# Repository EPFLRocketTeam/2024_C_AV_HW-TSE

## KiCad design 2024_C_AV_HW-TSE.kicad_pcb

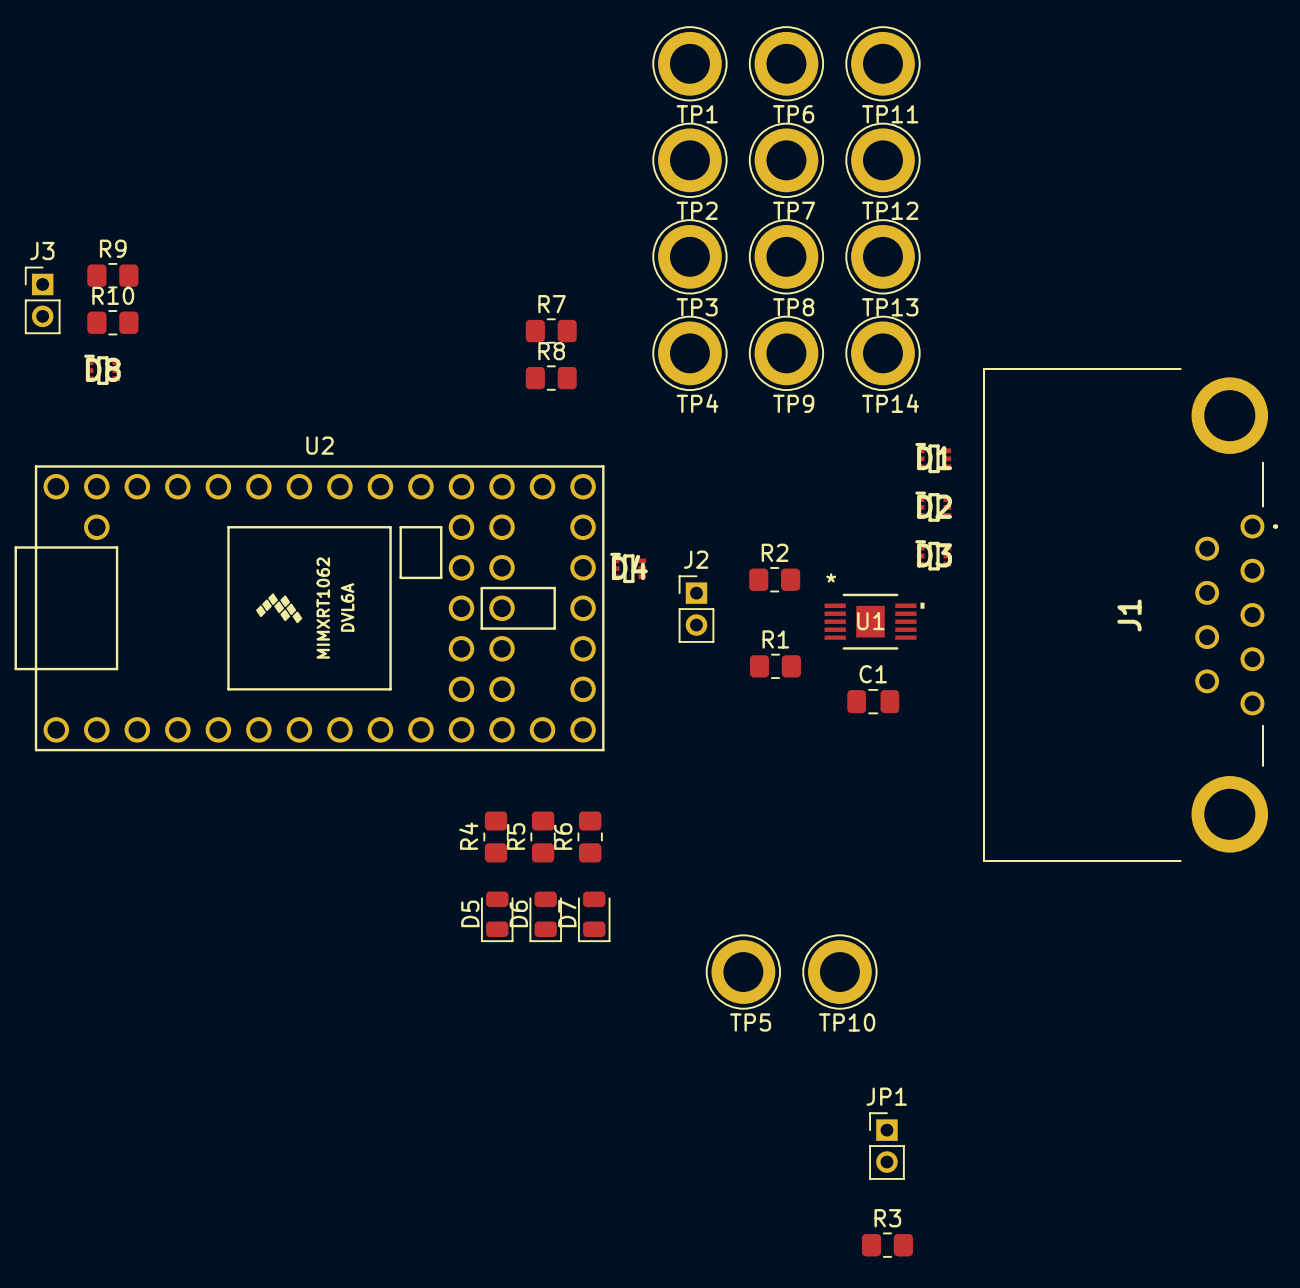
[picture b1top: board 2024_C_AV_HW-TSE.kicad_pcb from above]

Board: 2 copper layers, 39 parts (0 on the bottom side), 23 nets, no tracks yet.

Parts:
C1: 2.2u; C_0805_2012Metric_Pad1.18x1.45mm_HandSolder
D1, D2, D3, D4, D8: TPD2E1B06DRLR; SOTFL50P160X60-6N
D5, D6, D7: LED; LED_0805_2012Metric
J1: Spine Connector; G17C0910132EU
J2: I2C Bypass; PinHeader_1x02_P2.00mm_Vertical
J3: USART Bypass; PinHeader_1x02_P2.00mm_Vertical
JP1: Master/Slave Select; PinHeader_1x02_P2.00mm_Vertical
R1, R2: 4.7k; R_0805_2012Metric_Pad1.20x1.40mm_HandSolder
R3: 30k; R_0805_2012Metric_Pad1.20x1.40mm_HandSolder
R4, R5, R6: 220R; R_0805_2012Metric_Pad1.20x1.40mm_HandSolder
R7: 51k; R_0805_2012Metric_Pad1.20x1.40mm_HandSolder
R8: 47k; R_0805_2012Metric_Pad1.20x1.40mm_HandSolder
R9, R10: 0R; R_0805_2012Metric_Pad1.20x1.40mm_HandSolder
TP1: 5V Spine; TestPoint_Loop_D3.80mm_Drill2.5mm
TP2: 3V3 Spine; TestPoint_Loop_D3.80mm_Drill2.5mm
TP3: 5V Meas.; TestPoint_Loop_D3.80mm_Drill2.5mm
TP4: 3V3 Teensy; TestPoint_Loop_D3.80mm_Drill2.5mm
TP5: GND Ref; TestPoint_Loop_D3.80mm_Drill2.5mm
TP6: LED 1; TestPoint_Loop_D3.80mm_Drill2.5mm
TP7: LED 2; TestPoint_Loop_D3.80mm_Drill2.5mm
TP8: LED 3; TestPoint_Loop_D3.80mm_Drill2.5mm
TP9: CAN SCL H; TestPoint_Loop_D3.80mm_Drill2.5mm
TP10: CAN SCL L; TestPoint_Loop_D3.80mm_Drill2.5mm
TP11: CAN SDA H; TestPoint_Loop_D3.80mm_Drill2.5mm
TP12: CAN SDA L; TestPoint_Loop_D3.80mm_Drill2.5mm
TP13: SDA; TestPoint_Loop_D3.80mm_Drill2.5mm
TP14: SDL; TestPoint_Loop_D3.80mm_Drill2.5mm
U1: LT3960
U2: Teensy4.0; Teensy40

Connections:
+3.3V: C1.1, JP1.1 (A), R1.1, R2.1, TP4.1, U1.6 (VIN), U1.8 (VCC), U2.16 (3V3), U2.31 (3V3)
+3.3VP: D3.3 (NC_1), D3.4 (IOB2), J1.9, TP2.1, U2.22 (15_A1_RX3_SPDIF_IN)
+5VP: D3.1 (IOA1), D3.6 (NC_2), J1.1, R7.2, TP1.1
/5V_MEAS: R7.1, R8.2, TP3.1, U2.21 (14_A0_TX3_SPDIF_OUT)
/CAN_SCL_H: D1.1 (IOA1), D1.6 (NC_2), J1.8, TP9.1, U1.4 (CANSCLH)
/CAN_SCL_L: D1.3 (NC_1), D1.4 (IOB2), J1.3, TP10.1, U1.5 (CANSCLL)
/CAN_SDA_H: D2.1 (IOA1), D2.6 (NC_2), J1.7, TP11.1, U1.2 (CANSDAH)
/CAN_SDA_L: D2.3 (NC_1), D2.4 (IOB2), J1.2, TP12.1, U1.1 (CANSDAL)
/LED_1: R4.2, TP6.1, U2.12 (10_CS_MQSR)
/LED_2: R5.2, TP7.1, U2.13 (11_MOSI_CTX1)
/LED_3: R6.2, TP8.1, U2.14 (12_MISO_MQSL)
/MS: R3.2, U1.7 (EN/MODE)
/RX_Ta: D8.3 (NC_1), D8.4 (IOB2), J3.1, R9.1
/RX_Te: R10.2, U2.9 (7_RX2_OUT1A)
/SCL: D4.3 (NC_1), D4.4 (IOB2), J2.2, R2.2, TP14.1, U1.9 (SCL), U2.26 (19_A5_SCL0)
/SDA: D4.1 (IOA1), D4.6 (NC_2), J2.1, R1.2, TP13.1, U1.10 (SDA), U2.25 (18_A4_SDA0)
/TX_Ta: D8.1 (IOA1), D8.6 (NC_2), J3.2, R10.1
/TX_Te: R9.2, U2.10 (8_TX2_IN1)
GND: C1.2, D1.2 (IOB1), D1.5 (IOA2), D2.2 (IOB1), D2.5 (IOA2), D3.2 (IOB1), D3.5 (IOA2), D4.2 (IOB1), D4.5 (IOA2), D5.1 (K), D6.1 (K), D7.1 (K), D8.2 (IOB1), D8.5 (IOA2), J1.5, J1.6, J1.MH1, J1.MH2, R8.1, TP5.1, U1.3 (GND), U1.11 (GND), U2.1 (GND), U2.17 (GND), U2.32 (GND)
unnamed: D5.2 (A), R4.1
unnamed: D6.2 (A), R5.1
unnamed: D7.2 (A), R6.1
unnamed: JP1.2 (B), R3.1

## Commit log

2024-09-30 offline
2024-09-30 uart
2024-09-30 layout
